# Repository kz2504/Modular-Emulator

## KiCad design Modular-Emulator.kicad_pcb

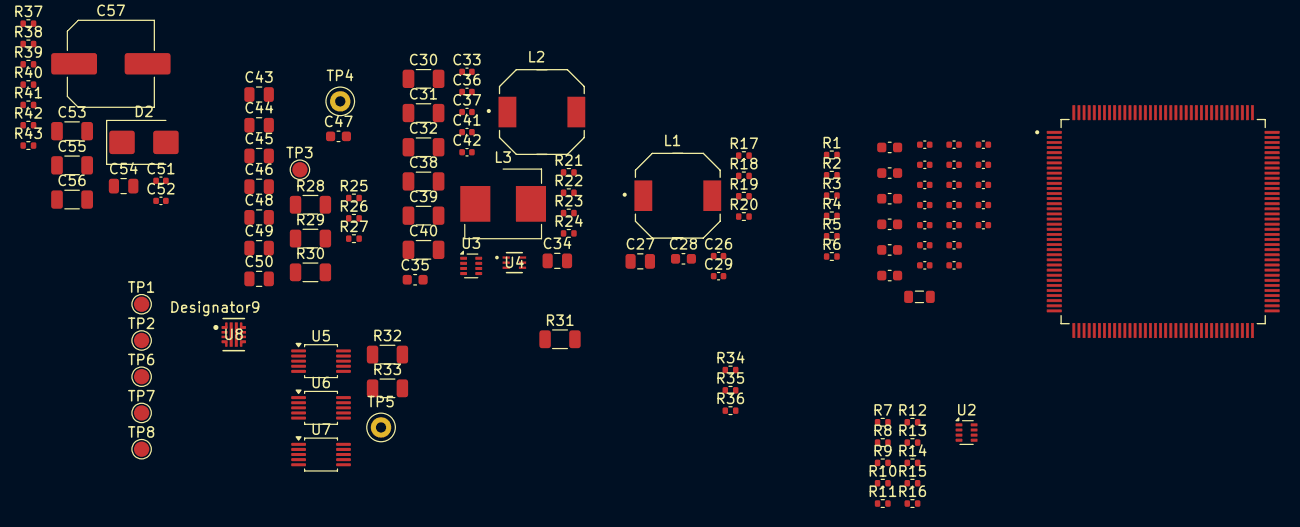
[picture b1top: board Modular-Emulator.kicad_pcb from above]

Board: 2 copper layers, 121 parts (0 on the bottom side), 51 nets, no tracks yet.

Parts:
C1, C2, C3, C4, C5, C6, C10, C11, C12, C13, C14, C15, C17, C18, C19, C20, C21, C22, C23, C29, C33, C37, C41, C42: 100nF; C_0402_1005Metric
C7, C8, C9, C16, C24, C25: 10uF; C_0603_1608Metric
C26, C36: 33nF; C_0402_1005Metric
C27, C34, C46, C48, C49, C50: 10uF; C_0805_2012Metric
C28, C35, C47: 100nF; C_0603_1608Metric
C30, C31, C32, C38, C39, C40: 22uF; C_1206_3216Metric
C43, C44, C45: 22uF; C_0805_2012Metric
C51: 2.2nF; C_0402_1005Metric
C52: 3.3nF; C_0402_1005Metric
C53: 1uF; C_1206_3216Metric
C54: 100nF; C_0805_2012Metric
C55, C56: 10uF; C_1206_3216Metric
C57: 470uF; C_Elec_8x10.2
D2: SMBJ13CA; D_SMB
FB1: 120R@100 MHz; L_0805_2012Metric
L1: 4.7uH; IND_1217AS-H-4R7N=P3
L2: 5.6uH; IND_1217AS-H-4R7N=P3
L3: 5.6uH; L_Wurth_WE-LHMI-7050
R1, R5, R6, R7, R8, R9, R11, R13, R14, R15, R16, R34, R35, R36: 4.7K; R_0402_1005Metric
R2, R3, R4: 0R; R_0402_1005Metric
R10: 1K; R_0402_1005Metric
R12: 22R; R_0402_1005Metric
R17, R21: 511K; R_0402_1005Metric
R18, R22: 88.7K; R_0402_1005Metric
R19: 31.3K; R_0402_1005Metric
R20, R24, R26: 10K; R_0402_1005Metric
R23: 52.3K; R_0402_1005Metric
R25: 8.25K; R_0402_1005Metric
R27: 100K; R_0402_1005Metric
R28, R29, R30: 0R; R_1206_3216Metric
R31, R32, R33: 5m; R_1206_3216Metric
R37: 665R; R_0402_1005Metric
R38, R40: 47K; R_0402_1005Metric
R39: 5.6K; R_0402_1005Metric
R41: 390K; R_0402_1005Metric
R42: 59K; R_0402_1005Metric
R43: 470K; R_0402_1005Metric
TP1, TP2, TP3, TP6, TP7, TP8: 1.5mm; TestPoint_Pad_D1.5mm
TP4, TP5: Keystone 5001; TestPoint_Keystone_5000-5004_Miniature
U1: LFE5U-25F-7TG144C; QFP50P2200X2200X160-144N
U2, U3: TPS62933F; SOT-583-8
U4: TPS563206DRLR; SOT_07SDRLR_TEX
U5, U6, U7: INA226; VSSOP-10_3x3mm_P0.5mm
U8: TPS259472LRPWR; RPW0010A-MFG

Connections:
+1V1: C1.1, C2.1, C3.1, C4.1, C5.1, C6.1, C7.1, C8.1, C9.1, R33.2, TP8.1, U1.20 (VCC), U1.29 (VCC), U1.38 (VCC), U1.66 (VCC), U1.83 (VCC), U1.130 (VCC), U7.8 (Vbus), U7.9 (Vin-)
+3V3: C14.1, C15.1, C17.1, C18.1, C19.1, C20.1, C21.1, C22.1, C23.1, C24.1, C25.1, R1.1, R5.1, R6.1, R7.1, R8.1, R9.1, R10.1, R11.1, R13.1, R14.1, R15.1, R31.2, R34.1, R35.1, R36.1, R38.1, TP6.1, U1.9 (VCCIO7), U1.16 (VCCIO6), U1.36 (VCCIO6), U1.43 (VCCIO8), U1.70 (VCCIO3), U1.86 (VCCIO3), U1.100 (VCCIO2), U1.122 (VCCIO1), U1.137 (VCCIO0), U5.6 (VS), U5.8 (Vbus), U5.9 (Vin-), U6.6 (VS), U7.6 (VS)
+5V: R32.2, TP7.1, U6.8 (Vbus), U6.9 (Vin-)
+12V: R28.1, R29.1, R30.1
/FPGA (CPU)/SN: R11.2, U1.48 (PB13A)
/FPGA (CPU)/TCK: R16.1, U1.63 (TCK)
/FPGA (CPU)/TDI: R13.2, U1.61 (TDI)
/FPGA (CPU)/TDO: R15.2, U1.60 (TDO)
/FPGA (CPU)/TMS: R14.2, U1.64 (TMS)
/Power Management/1V1_SHUNT-: C43.1, C44.1, C45.1, L3.2, R25.1, R33.1, TP2.1, U7.10 (Vin+)
/Power Management/3V3_SHUNT-: C30.1, C31.1, C32.1, C33.1, L1.2, R19.1, R31.1, TP3.1, U5.10 (Vin+)
/Power Management/5V_SHUNT-: C38.1, C39.1, C40.1, C41.1, L2.2, R23.1, R32.1, TP1.1, U6.10 (Vin+)
/Power Management/ALERT_1V1: R34.2, R35.2, R36.2, U5.3 (~Alert), U6.3 (~Alert), U7.3 (~Alert)
/Power Management/PG: R38.2, U8.3 (PG)
/Power Management/SCL: U5.5 (SCL), U6.5 (SCL), U7.5 (SCL)
/Power Management/SDA: U5.4 (SDA), U6.4 (SDA), U7.4 (SDA)
GND: C1.2, C2.2, C3.2, C4.2, C5.2, C6.2, C7.2, C8.2, C9.2, C10.2, C11.2, C12.2, C13.2, C14.2, C15.2, C16.2, C17.2, C18.2, C19.2, C20.2, C21.2, C22.2, C23.2, C24.2, C25.2, C26.2, C27.2, C28.2, C30.2, C31.2, C32.2, C33.2, C34.2, C35.2, C36.2, C38.2, C39.2, C40.2, C41.2, C43.2, C44.2, C45.2, C46.2, C47.2, C48.2, C49.2, C50.2, C51.1, C52.1, C53.2, C54.2, C55.2, C56.2, C57.2, D2.2 (A), R2.2, R3.2, R4.2, R16.2, R18.2, R20.2, R22.2, R24.2, R26.2, R37.2, R39.2, R41.1, R42.1, TP4.1, TP5.1, U1.8 (GND), U1.15 (GND), U1.21 (GND), U1.32 (VSSIO6), U1.42 (GND), U1.65 (GND), U1.75 (GND), U1.85 (GND), U1.87 (GND), U1.101 (GND), U1.123 (GND), U1.129 (GND), U1.131 (GND), U1.138 (GND), U2.4 (GND), U3.4 (GND), U4.3 (GND), U5.1 (A1), U5.2 (A0), U5.7 (GND), U6.1 (A1), U6.2 (A0), U6.7 (GND), U7.1 (A1), U7.2 (A0), U7.7 (GND), U8.8 (GND)
unnamed: C53.1, C54.1, D2.1 (K), R43.2, U8.5 (IN)
unnamed: R10.2, U1.54 (CCLK)
unnamed: R1.2, R4.1, U1.62 (CFG_0)
unnamed: R3.1, R6.2, U1.59 (CFG_1)
unnamed: R2.1, R5.2, U1.58 (CFG_2)
unnamed: R8.2, U1.56 (DONE)
unnamed: R12.1, U1.46 (PB11A)
unnamed: R9.2, U1.55 (~INIT)
unnamed: R7.2, U1.57 (~PROGRAM)
unnamed: C29.1, U2.6 (BST)
unnamed: R17.2, R18.1, U2.2 (EN)
unnamed: R19.2, R20.1, U2.8 (FB)
unnamed: C26.1, U2.7 (SS)
unnamed: C29.2, L1.1, U2.5 (SW)
unnamed: C27.1, C28.1, C50.1, R17.1, R28.2, U2.3 (VIN)
unnamed: C37.1, U3.6 (BST)
unnamed: R21.2, R22.1, U3.2 (EN)
unnamed: R23.2, R24.1, U3.8 (FB)
unnamed: C36.1, U3.7 (SS)
unnamed: C37.2, L2.1, U3.5 (SW)
unnamed: C34.1, C35.1, C49.1, R21.1, R29.2, U3.3 (VIN)
unnamed: C42.1, U4.4 (BST)
unnamed: R27.2, U4.5 (EN)
unnamed: R25.2, R26.1, U4.6 (FB)
unnamed: C42.2, L3.1, U4.2 (SW)
unnamed: C46.1, C47.1, C48.1, R27.1, R30.2, U4.1 (VIN)
unnamed: R42.2, R43.1, U8.1 (EN_UVLO)
unnamed: R37.1, U8.9 (ILM)
unnamed: C51.2, U8.10 (ITIMER)
unnamed: C55.1, C56.1, C57.1, R40.2, U8.6 (OUT)
unnamed: R41.2, U8.2 (OVCSEL)
unnamed: R39.1, R40.1, U8.4 (PGTH)
unnamed: C52.2, U8.7 (dVdt)
VCCAUX: C10.1, C11.1, C12.1, C13.1, C16.1, FB1.2, U1.17 (VCCAUX), U1.53 (VCCAUX), U1.96 (VCCAUX), U1.132 (VCCAUX)
